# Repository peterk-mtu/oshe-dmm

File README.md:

# oshe-dmm
open source hardware enterprise digital multimeter project

# Photo of our proposed design

# Screenshot of the start to our PCB design

# Screenshot of the Final PCB design

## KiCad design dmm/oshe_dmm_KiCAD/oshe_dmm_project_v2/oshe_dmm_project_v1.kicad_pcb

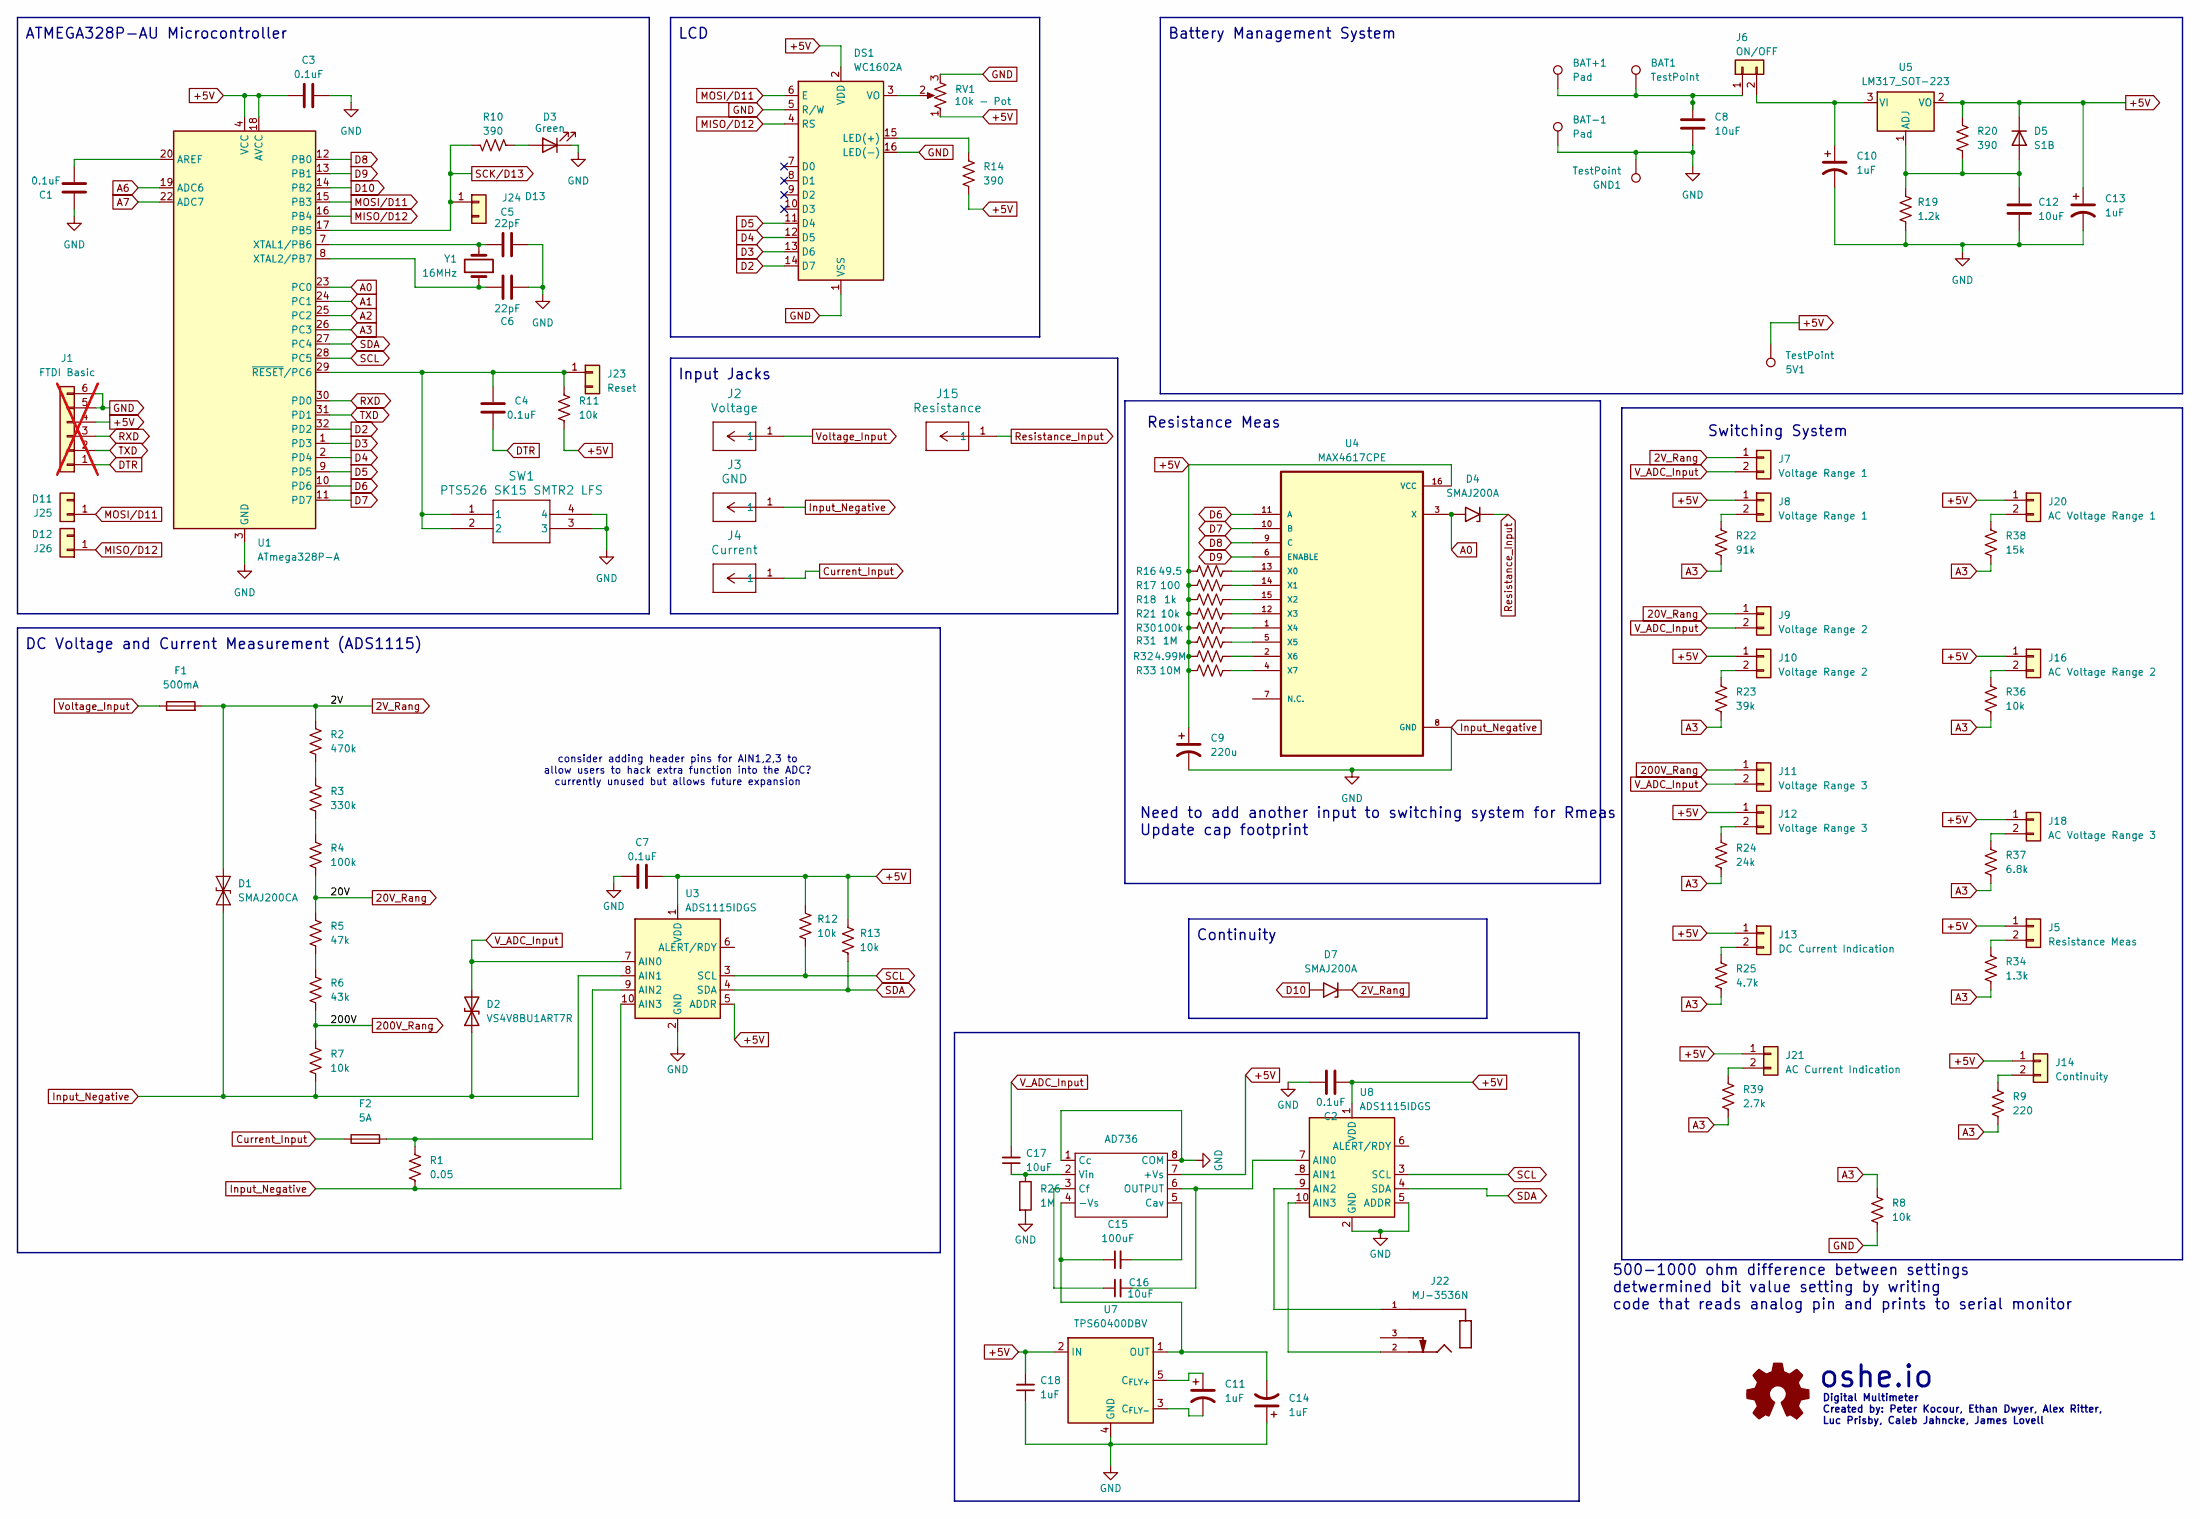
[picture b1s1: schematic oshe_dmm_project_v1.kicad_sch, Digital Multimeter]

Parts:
5V1: TestPoint; TestPoint_Keystone_5019_Minature
BAT1: TestPoint; TestPoint_Keystone_5019_Minature
BAT+1: Pad; TestPoint_THTPad_D4.0mm_Drill2.0mm
BAT-1: Pad; TestPoint_THTPad_D4.0mm_Drill2.0mm
C1, C2, C3, C4, C7: 0.1uF; C_1206_3216Metric_Pad1.33x1.80mm_HandSolder
C5, C6: 22pF; C_1206_3216Metric_Pad1.33x1.80mm_HandSolder
C8, C12, C16, C17: 10uF; C_1206_3216Metric_Pad1.33x1.80mm_HandSolder
C9: 220u; CP_Radial_D6.3mm_P2.50mm
C10, C11, C13, C14, C18: 1uF; CP_Elec_4x4.5
C15: 100uF; CAPC3216X190N
D1: SMAJ200CA; D_SMA
D2: VS4V8BU1ART7R; D_0805_2012Metric_Pad1.15x1.40mm_HandSolder
D3: Green; LED_1206_3216Metric_Pad1.42x1.75mm_HandSolder
D4, D7: SMAJ200A; D_SMA
D5: S1B; D_SMA
DS1: WC1602A
F1: 500mA; FUSE_4628
F2: 5A; FUSE_4628
GND1: TestPoint; TestPoint_Keystone_5019_Minature
J1: FTDI Basic; PinSocket_1x06_P2.54mm_Vertical; not fitted
J2: Voltage; CONN_575-8_KEY
J3: GND; CONN_575-8_KEY
J4: Current; CONN_575-8_KEY
J5: Resistance Meas; PinHeader_1x02_P2.54mm_Vertical
J6: ON/OFF; PinHeader_1x02_P2.54mm_Vertical
J7, J8: Voltage Range 1; PinHeader_1x02_P2.54mm_Vertical
J9, J10: Voltage Range 2; PinHeader_1x02_P2.54mm_Vertical
J11, J12: Voltage Range 3; PinHeader_1x02_P2.54mm_Vertical
J13: DC Current Indication; PinHeader_1x02_P2.54mm_Vertical
J14: Continuity; PinHeader_1x02_P2.54mm_Vertical
J15: Resistance; CONN_575-8_KEY
J16: AC Voltage Range 2; PinHeader_1x02_P2.54mm_Vertical
J18: AC Voltage Range 3; PinHeader_1x02_P2.54mm_Vertical
J20: AC Voltage Range 1; PinHeader_1x02_P2.54mm_Vertical
J21: AC Current Indication; PinHeader_1x02_P2.54mm_Vertical
J22: MJ-3536N; SAMESKY_MJ-3536N; PARTREV 1.05
J23: Reset; PinHeader_1x01_P2.54mm_Vertical
J24: D13; PinHeader_1x01_P2.54mm_Vertical
J25: D11; PinHeader_1x01_P2.54mm_Vertical
J26: D12; PinHeader_1x01_P2.54mm_Vertical
R1: 0.05; R_2512_6332Metric_Pad1.40x3.35mm_HandSolder
R2: 470k; R_1206_3216Metric_Pad1.30x1.75mm_HandSolder
R3: 330k; R_1206_3216Metric_Pad1.30x1.75mm_HandSolder
R4, R30: 100k; R_1206_3216Metric_Pad1.30x1.75mm_HandSolder
R5: 47k; R_1206_3216Metric_Pad1.30x1.75mm_HandSolder
R6: 43k; R_1206_3216Metric_Pad1.30x1.75mm_HandSolder
R7, R8, R11, R12, R13, R21, R36: 10k; R_1206_3216Metric_Pad1.30x1.75mm_HandSolder
R9: 220; R_1206_3216Metric_Pad1.30x1.75mm_HandSolder
R10, R14, R20: 390; R_1206_3216Metric_Pad1.30x1.75mm_HandSolder
R16: 49.5; R_1206_3216Metric_Pad1.30x1.75mm_HandSolder
R17: 100; R_1206_3216Metric_Pad1.30x1.75mm_HandSolder
R18: 1k; R_1206_3216Metric_Pad1.30x1.75mm_HandSolder
R19: 1.2k; R_1206_3216Metric_Pad1.30x1.75mm_HandSolder
R22: 91k; R_1206_3216Metric_Pad1.30x1.75mm_HandSolder
R23: 39k; R_1206_3216Metric_Pad1.30x1.75mm_HandSolder
R24: 24k; R_1206_3216Metric_Pad1.30x1.75mm_HandSolder
R25: 4.7k; R_1206_3216Metric_Pad1.30x1.75mm_HandSolder
R26, R31: 1M; R_1206_3216Metric_Pad1.30x1.75mm_HandSolder
R32: 4.99M; R_1206_3216Metric_Pad1.30x1.75mm_HandSolder
R33: 10M; R_1206_3216Metric_Pad1.30x1.75mm_HandSolder
R34: 1.3k; R_1206_3216Metric_Pad1.30x1.75mm_HandSolder
R37: 6.8k; R_1206_3216Metric_Pad1.30x1.75mm_HandSolder
R38: 15k; R_1206_3216Metric_Pad1.30x1.75mm_HandSolder
R39: 2.7k; R_1206_3216Metric_Pad1.30x1.75mm_HandSolder
RV1: 10k - Pot; Potentiometer_Bourns_3266Y_Vertical
SW1: PTS526 SK15 SMTR2 LFS; SMT_FS
U1: ATmega328P-A; TQFP-32_7x7mm_P0.8mm
U2: AD736; PDIP-8_N
U3, U8: ADS1115IDGS; MODULE_ZC261500
U4: MAX4617CPE
U5: LM317_SOT-223; SOT-223-3_TabPin2
U7: TPS60400DBV; SOT-23-5
Y1: 16MHz; Crystal_HC49-U_Vertical

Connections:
2V_Rang: D1.1 (A1), D7.1 (A1), F1.2, J7.1, R2.1
20V_Rang: J9.1, R4.2, R5.1
200V_Rang: J11.1, R6.2, R7.1
+5V: 5V1.1, C2.1, C3.1, C7.2, C9.1, C13.1, C18.2, D5.1 (K), DS1.2 (VDD), J1.4, J5.1, J8.1, J10.1, J12.1, J13.1, J14.1, J16.1, J18.1, J20.1, J21.1, R11.2, R12.1, R13.1, R14.1, R16.1, R17.1, R18.1, R20.1, R21.1, R30.1, R31.1, R32.1, R33.1, RV1.1, U1.4 (VCC), U1.6 (VCC), U1.18 (AVCC), U2.7 (+Vs), U3.1 (VDD), U3.5 (ADDR), U4.16 (VCC), U5.2 (VO), U7.2 (IN), U8.1 (VDD)
A0: D4.2 (A2), U1.23 (PC0), U4.3 (X)
A1: U1.24 (PC1)
A2: U1.25 (PC2)
A3: R8.2, R9.1, R22.1, R23.1, R24.1, R25.1, R34.1, R36.1, R37.1, R38.1, R39.1, U1.26 (PC3)
A6: U1.19 (ADC6)
A7: U1.22 (ADC7)
Current_Input: F2.1, J4.1
D2: DS1.14 (D7), U1.32 (PD2)
D3: DS1.13 (D6), U1.1 (PD3)
D4: DS1.12 (D5), U1.2 (PD4)
D5: DS1.11 (D4), U1.9 (PD5)
D6: U1.10 (PD6), U4.11 (A)
D7: U1.11 (PD7), U4.10 (B)
D8: U1.12 (PB0), U4.9 (C)
D9: U1.13 (PB1), U4.6 (ENABLE)
D10: D7.2 (A2), U1.14 (PB2)
DTR: C4.2, J1.1
GND: BAT-1.1, C1.1, C2.2, C3.2, C5.2, C6.1, C7.1, C8.2, C9.2, C10.2, C12.2, C13.2, C14.1, C18.1, D1.2 (A2), D2.1 (A1), D3.1 (K), DS1.1 (VSS), DS1.5 (R/W), DS1.16 (LED(-)), GND1.1, J1.5, J1.6, J3.1, R1.2, R7.2, R8.1, R19.2, R26.2, RV1.3, SW1.3, SW1.4, U1.3 (GND), U1.5 (GND), U1.21 (GND), U2.1 (Cc), U2.8 (COM), U3.2 (GND), U3.8 (AIN1), U3.10 (AIN3), U4.8 (GND), U7.4 (GND), U8.2 (GND), U8.5 (ADDR)
MISO/D12: DS1.4 (RS), J26.1, U1.16 (PB4)
MOSI/D11: DS1.6 (E), J25.1, U1.15 (PB3)
unnamed: D3.2 (A), R10.1
unnamed: C12.1, D5.2 (A), R19.1, R20.2, U5.1 (ADJ)
unnamed: DS1.15 (LED(+)), R14.2
unnamed: DS1.3 (VO), RV1.2
unnamed: J5.2, R34.2
unnamed: BAT1.1, BAT+1.1, C8.1, J6.1
unnamed: C10.1, J6.2, U5.3 (VI)
unnamed: J8.2, R22.2
unnamed: J10.2, R23.2
unnamed: J12.2, R24.2
unnamed: J13.2, R25.2
unnamed: J14.2, R9.2
unnamed: J16.2, R36.2
unnamed: J18.2, R37.2
unnamed: J20.2, R38.2
unnamed: J21.2, R39.2
unnamed: C4.1, J23.1, R11.1, SW1.1, SW1.2, U1.29 (~RESET/PC6)
unnamed: R2.2, R3.1
unnamed: R3.2, R4.1
unnamed: R5.2, R6.1
unnamed: C1.2, U1.20 (AREF)
unnamed: C5.1, U1.7 (XTAL1/PB6), Y1.2
unnamed: C6.2, U1.8 (XTAL2/PB7), Y1.1
unnamed: C14.2, C15.1, U2.4 (-Vs), U7.1 (OUT)
unnamed: C15.2, U2.5 (Cav)
unnamed: C16.1, U2.3 (Cf)
unnamed: C16.2, U2.6 (OUTPUT), U8.7 (AIN0)
unnamed: C17.1, R26.1, U2.2 (Vin)
unnamed: F2.2, R1.1, U3.9 (AIN2)
unnamed: R16.2, U4.13 (X0)
unnamed: R17.2, U4.14 (X1)
unnamed: R18.2, U4.15 (X2)
unnamed: R21.2, U4.12 (X3)
unnamed: R30.2, U4.1 (X4)
unnamed: R31.2, U4.5 (X5)
unnamed: R32.2, U4.2 (X6)
unnamed: R33.2, U4.4 (X7)
unnamed: C11.1, U7.5 (C_{FLY+})
unnamed: C11.2, U7.3 (C_{FLY-})
unnamed: J22.1, U8.9 (AIN2)
unnamed: J22.2, U8.10 (AIN3)
RXD: J1.3, U1.30 (PD0)
Resistance_Input: D4.1 (A1), J15.1
SCK/D13: J24.1, R10.2, U1.17 (PB5)
SCL: R12.2, U1.28 (PC5), U3.3 (SCL), U8.3 (SCL)
SDA: R13.2, U1.27 (PC4), U3.4 (SDA), U8.4 (SDA)
TXD: J1.2, U1.31 (PD1)
V_ADC_Input: C17.2, D2.2 (A2), J7.2, J9.2, J11.2, U3.7 (AIN0)
Voltage_Input: F1.1, J2.1

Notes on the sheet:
Digital Multimeter Created by: Peter Kocour, Ethan Dwyer, Alex Ritter, Luc Prisby, Caleb Jahncke, James Lovell
Need to add another input to switching system for Rmeas Update cap footprint
consider adding header pins for AIN1,2,3 to allow users to hack extra function into the ADC? currently unused but allows future expansion
Resistance Meas
oshe.io
Switching System
Battery Management System
DC Voltage and Current Measurement (ADS1115)
LCD
500-1000 ohm difference between settings detwermined bit value setting by writing code that reads analog pin and prints to serial monitor
Input Jacks
Continuity
ATMEGA328P-AU Microcontroller

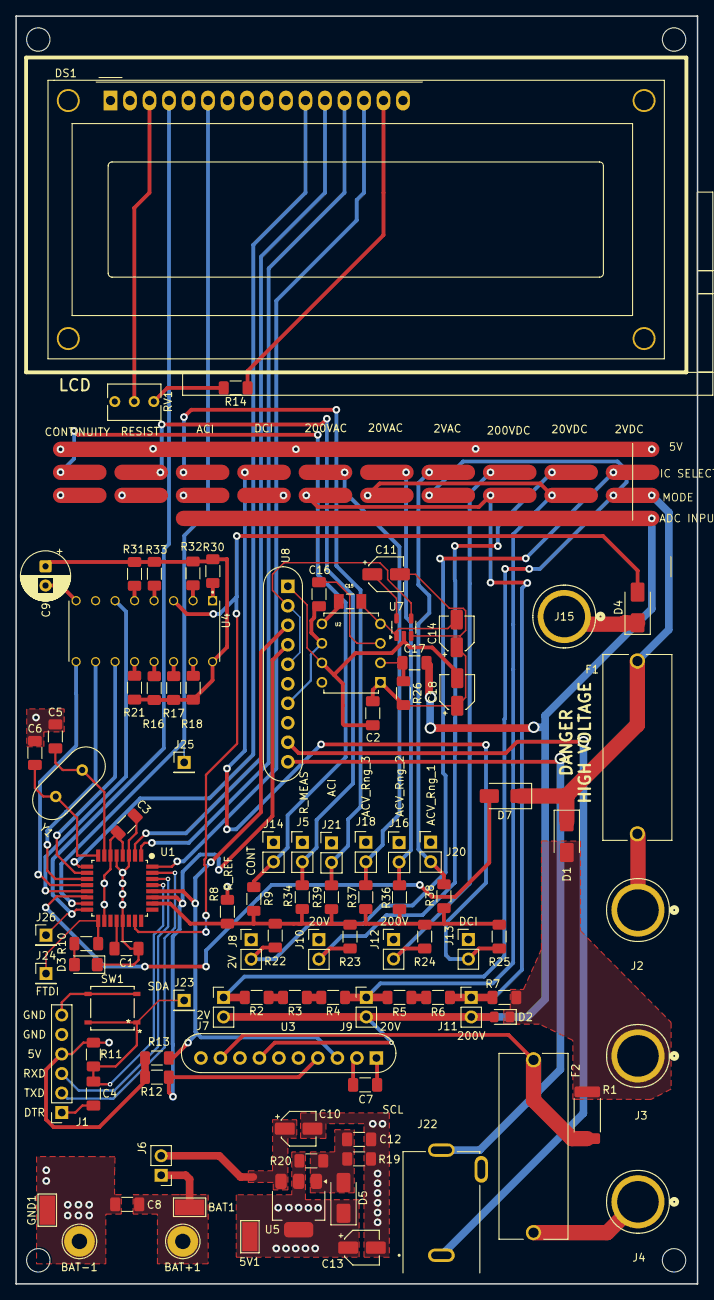
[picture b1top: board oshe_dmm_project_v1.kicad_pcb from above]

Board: 4 copper layers, 88.7 x 165.1 mm, 100 parts (0 on the bottom side), 69 nets.

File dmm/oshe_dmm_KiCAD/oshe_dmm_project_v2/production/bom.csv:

Designator,Footprint,Quantity,Value,LCSC Part #
"5V1, BAT1, GND1",TestPoint_Keystone_5019_Minature,3,TestPoint,
"BAT+1, BAT-1, THERMISTOR1",TestPoint_THTPad_D4.0mm_Drill2.0mm,3,Pad,
"C1, C2, C3, C4, C7",1206,5,0.1uF,
"C10, C11, C13, C14, C18",CP_Elec_4x4.5,5,1uF,
"C12, C16, C17, C8",1206,4,10uF,
C15,CAPC3216X190N,1,100uF,
"C5, C6",1206,2,22pF,
C9,CP_Radial_D6.3mm_P2.50mm,1,220u,
D1,D_SMA,1,SMAJ200CA,
D2,0805,1,VS4V8BU1ART7R,
D3,1206,1,Green,
"D4, D7",D_SMA,2,SMAJ200A,
D5,D_SMA,1,S1B,
DS1,WC1602A,1,WC1602A,
F1,FUSE_4628,1,500mA,
F2,FUSE_4628,1,5A,
J1,PinSocket_1x06_P2.54mm_Vertical,1,FTDI Basic,
"J10, J9",PinHeader_1x02_P2.54mm_Vertical,2,Voltage Range 2,
"J11, J12",PinHeader_1x02_P2.54mm_Vertical,2,Voltage Range 3,
J13,PinHeader_1x02_P2.54mm_Vertical,1,DC Current Indication,
J14,PinHeader_1x02_P2.54mm_Vertical,1,Continuity,
J16,PinHeader_1x02_P2.54mm_Vertical,1,AC Voltage Range 2,
J18,PinHeader_1x02_P2.54mm_Vertical,1,AC Voltage Range 3,
J2,CONN_575-8_KEY,1,Voltage,
J20,PinHeader_1x02_P2.54mm_Vertical,1,AC Voltage Range 1,
J21,PinHeader_1x02_P2.54mm_Vertical,1,AC Current Indication,
J22,SAMESKY_MJ-3536N,1,MJ-3536N,
J3,CONN_575-8_KEY,1,GND,
J4,CONN_575-8_KEY,1,Current,
J5,PinHeader_1x02_P2.54mm_Vertical,1,Resistance Meas,
J6,PinHeader_1x02_P2.54mm_Vertical,1,ON/OFF,
"J7, J8",PinHeader_1x02_P2.54mm_Vertical,2,Voltage Range 1,
R1,2512,1,0.05,
"R10, R14, R20",1206,3,390,
"R11, R12, R13, R15, R21, R7",1206,6,10k,
R16,1206,1,49.5,
R17,1206,1,100,
"R18, R8",1206,2,1k,
"R19, R24",1206,2,1.2k,
R2,1206,1,470k,
R22,1206,1,180,
R23,1206,1,680,
"R25, R34, R39, R9",1206,4,R?,
"R26, R31",1206,2,1M,
R3,1206,1,330k,
"R30, R4",1206,2,100k,
R32,1206,1,4.99M,
R33,1206,1,10M,
R36,1206,1,2.4k,
R37,1206,1,3k,
R38,1206,1,1.8k,
R5,1206,1,47k,
R6,1206,1,43k,
RV1,Potentiometer_Bourns_3266Y_Vertical,1,10k - Pot,
SW1,SMT_FS,1,PTS526 SK15 SMTR2 LFS,
U1,TQFP-32_7x7mm_P0.8mm,1,ATmega328P-A,
U2,PDIP-8_N,1,AD736,
"U3, U8",MODULE_ZC261500,2,ADS1115IDGS,
U4,DIP794W47P254L1943H457Q16,1,MAX4617CPE,
U5,SOT-223-3_TabPin2,1,LM317_SOT-223,
U7,SOT-23-5,1,TPS60400DBV,
Y1,Crystal_HC49-U_Vertical,1,16MHz,

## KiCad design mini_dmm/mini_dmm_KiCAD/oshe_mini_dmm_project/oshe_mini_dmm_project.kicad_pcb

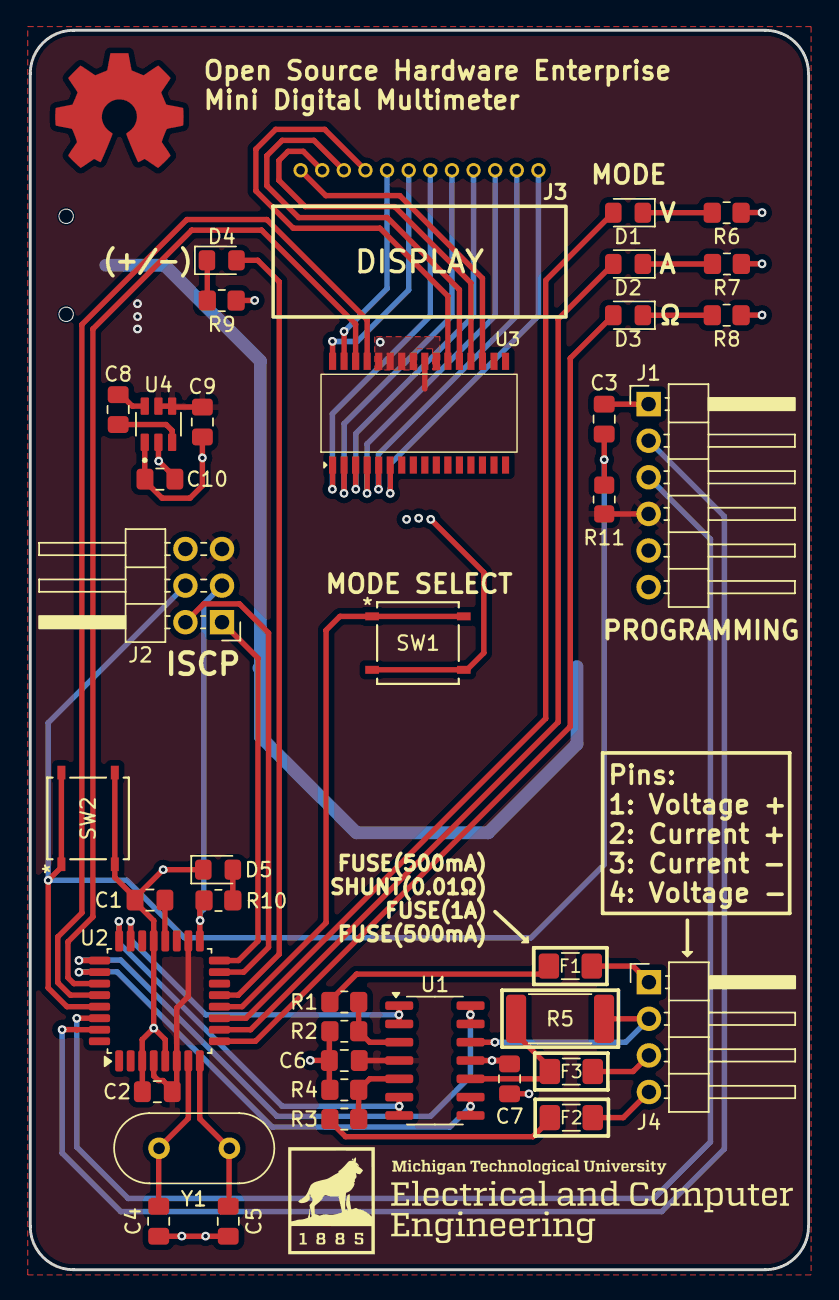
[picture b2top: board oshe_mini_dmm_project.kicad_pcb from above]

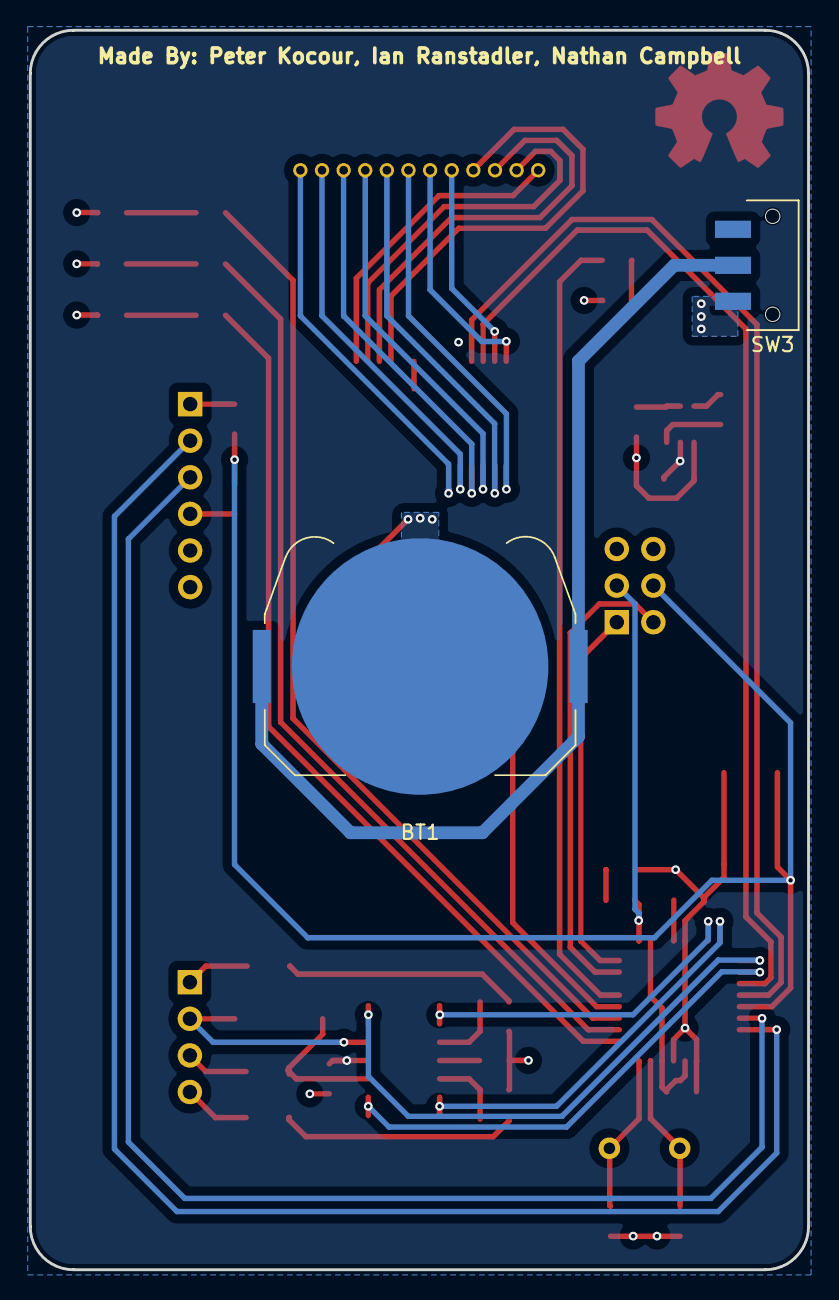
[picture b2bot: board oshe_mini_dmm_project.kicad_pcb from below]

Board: 4 copper layers, 54.0 x 86.0 mm, 42 parts (2 on the bottom side), 53 nets.

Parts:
BT1: Battery; BatteryHolder_Keystone_3034_1x20mm
C1, C2, C3: 0.1uF; C_0805_2012Metric_Pad1.18x1.45mm_HandSolder
C4, C5: 22pF; C_0805_2012Metric_Pad1.18x1.45mm_HandSolder
C6, C7: 1uF; C_0805_2012Metric_Pad1.18x1.45mm_HandSolder
C8, C9, C10: 10uF; C_0805_2012Metric_Pad1.18x1.45mm_HandSolder
D1: VOLTAGE; LED_0805_2012Metric_Pad1.15x1.40mm_HandSolder
D2: CURRENT; LED_0805_2012Metric_Pad1.15x1.40mm_HandSolder
D3: RESISTANCE; LED_0805_2012Metric_Pad1.15x1.40mm_HandSolder
D4: NEGATIVE; LED_0805_2012Metric_Pad1.15x1.40mm_HandSolder
D5: Green; LED_0805_2012Metric_Pad1.15x1.40mm_HandSolder
F1, F2: 500mA; Fuse_1206_3216Metric_Pad1.42x1.75mm_HandSolder
F3: 1A; Fuse_1206_3216Metric_Pad1.42x1.75mm_HandSolder
J1: FTDI Basic; PinHeader_1x06_P2.54mm_Horizontal
J2: ICSP; PinHeader_2x03_P2.54mm_Horizontal
J3: DISPLAY; LCD-S401M16KR-81359
J4: TEST LEAD CONNECTIONS; PinHeader_1x04_P2.54mm_Horizontal
R1, R3: 9.1MEG; R_0805_2012Metric_Pad1.20x1.40mm_HandSolder
R2, R4: 1MEG; R_0805_2012Metric_Pad1.20x1.40mm_HandSolder
R5: 0.05; R_2512_6332Metric_Pad1.40x3.35mm_HandSolder
R6, R7, R8, R9: 1k; R_0805_2012Metric_Pad1.20x1.40mm_HandSolder
R10: 390; R_0805_2012Metric_Pad1.20x1.40mm_HandSolder
R11: 10k; R_0805_2012Metric_Pad1.20x1.40mm_HandSolder
SW1, SW2: PTS526 SK15 SMTR2 LFS; SMT_FS
SW3: SW_DPDT_x2; SW_JS102011SAQN
U1: LM324; SOIC-14_3.9x8.7mm_P1.27mm
U2: ATmega328P-A; TQFP-32_7x7mm_P0.8mm
U3: BU91796FS-ME2; SSOP-A32
U4: LM2664M6; SOT95P280X145-6N
Y1: 16MHz; Crystal_HC49-U_Vertical

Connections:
+3.3V: C2.1, C6.2, C9.2, J1.4, J2.5, R11.2, SW3.1 (A), U1.4 (V+), U2.4 (VCC), U2.6 (VCC), U2.18 (AVCC), U3.24 (VDD), U4.4 (~SD), U4.5 (V+)
-3.3V: C7.1, C10.2, U1.11 (V-), U4.2 (OUT)
/Clock+: C4.1, U2.7 (XTAL1/PB6), Y1.2
/Clock-: C5.2, U2.8 (XTAL2/PB7), Y1.1
A0: U1.1, U1.2 (-), U2.23 (PC0)
A1: U1.6 (-), U1.7, U2.24 (PC1)
A2: U1.13 (-), U1.14, U2.25 (PC2)
A3: U1.8, U1.9 (-), U2.26 (PC3)
A4/SDA: U2.27 (PC4), U3.30 (SDA)
A5/SCL: U2.28 (PC5), U3.29 (SCL)
COM0: J3.1, U3.19 (COM_0)
COM1: J3.2, U3.20 (COM_1)
COM2: J3.3, U3.21 (COM_2)
COM3: J3.4, U3.22 (COM_3)
D5: D3.2 (A), U2.9 (PD5)
D6: D2.2 (A), U2.10 (PD6)
D7: D1.2 (A), U2.11 (PD7)
D8: SW1.1, SW1.2, U2.12 (PB0)
D9: D4.2 (A), U2.13 (PB1)
DTR: C3.2, J1.1
GND: BT1.2 (-), C1.1, C2.2, C4.2, C5.1, C6.1, C7.2, C9.1, C10.1, D5.1 (K), J1.5, J1.6, J2.6, R2.2, R4.2, R6.1, R7.1, R8.1, R9.1, SW1.3, SW1.4, SW2.3, SW2.4, U2.3 (GND), U2.5 (GND), U2.21 (GND), U3.23 (VLCD), U3.25 (VSS), U3.26 (TEST_1), U3.27 (TEST_2), U3.28 (OSCIN), U4.1 (GND)
LEAD_1: F1.1, J4.1
LEAD_2: F2.1, J4.4
LEAD_3: F3.1, J4.3
LEAD_4: J4.2, R5.2, U1.12 (+)
MISO/D12: J2.1, U2.16 (PB4)
MOSI/D11: J2.2, U2.15 (PB3)
unnamed: BT1.1 (+), SW3.2 (B)
unnamed: D1.1 (K), R6.2
unnamed: D2.1 (K), R7.2
unnamed: D3.1 (K), R8.2
unnamed: D4.1 (K), R9.2
unnamed: D5.2 (A), R10.1
unnamed: F1.2, R1.1
unnamed: F2.2, R3.1
unnamed: R1.2, R2.1, U1.3 (+)
unnamed: R3.2, R4.1, U1.5 (+)
unnamed: F3.2, R5.1, U1.10 (+)
unnamed: C1.2, U2.20 (AREF)
unnamed: C8.1, U4.6 (CAP+)
unnamed: C8.2, U4.3 (CAP-)
RESET: C3.1, J2.4, R11.1, SW2.1, SW2.2, U2.29 (~RESET/PC6)
RXD: J1.3, U2.30 (PD0)
SCK/D13: J2.3, R10.2, U2.17 (PB5)
SEG0: J3.5, U3.31 (SEG_0)
SEG1: J3.6, U3.32 (SEG_1)
SEG2: J3.7, U3.1 (SEG_2)
SEG3: J3.8, U3.2 (SEG_3)
SEG4: J3.9, U3.3 (SEG_4)
SEG5: J3.10, U3.4 (SEG_5)
SEG6: J3.11, U3.5 (SEG_6)
SEG7: J3.12, U3.6 (SEG_7)
TXD: J1.2, U2.31 (PD1)

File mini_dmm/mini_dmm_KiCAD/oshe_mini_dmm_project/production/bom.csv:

Designator,Footprint,Quantity,Value,LCSC Part #
BT1,BatteryHolder_Keystone_3034_1x20mm,1,Battery,
"C1, C2, C3",0805,3,0.1uF,
"C10, C8, C9",0805,3,10uF,
"C4, C5",0805,2,22pF,
"C6, C7",0805,2,1uF,
D1,0805,1,VOLTAGE,
D2,0805,1,CURRENT,
D3,0805,1,RESISTANCE,
D4,0805,1,NEGATIVE,
D5,0805,1,Green,
"F1, F2",1206,2,500mA,
F3,1206,1,1A,
J1,PinHeader_1x06_P2.54mm_Horizontal,1,FTDI Basic,
J2,PinHeader_2x03_P2.54mm_Horizontal,1,ICSP,
J3,LCD-S401M16KR-81359,1,DISPLAY,
J4,PinHeader_1x04_P2.54mm_Horizontal,1,TEST LEAD CONNECTIONS,
"R1, R3",0805,2,9.1MEG,
R10,0805,1,390,
R11,0805,1,10k,
"R2, R4",0805,2,1MEG,
R5,2512,1,0.05,
"R6, R7, R8, R9",0805,4,1k,
"SW1, SW2",SMT_FS,2,PTS526 SK15 SMTR2 LFS,
SW3,SW_JS102011SAQN,1,SW_DPDT_x2,
U1,SOIC-14_3.9x8.7mm_P1.27mm,1,LM324,
U2,TQFP-32_7x7mm_P0.8mm,1,ATmega328P-A,
U3,SSOP-A32,1,BU91796FS-ME2,
U4,SOT95P280X145-6N,1,LM2664M6,
Y1,Crystal_HC49-U_Vertical,1,16MHz,

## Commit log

2025-02-07 Created the kicad project files
2025-02-07 Added photos folder and a photo
2025-02-07 Changed photo name
2025-02-07 Fixed README.md
2025-02-07 Started the primary schematic file
2025-02-08 Added BMS to schematic
2025-02-10 Updated main schematic
2025-02-10 Updated things?
2025-02-10 Created an initial PCB
2025-02-10 Made some changes to the PCB
2025-02-10 Made more PCB changes
2025-02-10 Made more changes
2025-02-12 Changed some stuff
2025-02-12 Update Current_Measurement.kicad_sch
    deleted
2025-02-13 Added Current Measurement
2025-02-13 just opened the file
2025-02-13 Took a look at things
2025-02-17 Opened files
2025-02-19 Made changes to PCB and Schematic
2025-02-19 changed resitor symbols
2025-02-19 Made some PCB changes
2025-02-21 Made some changes
2025-02-23 Worked on the PCB
2025-02-24 PCB Design Work
2025-02-25 Made some more PCB changes
2025-02-27 Finalized the BMS system
2025-02-28 Updated input protection schematic.
2025-02-28 Checked some changes
2025-02-28 Made some PCB design changes
2025-02-28 Update Voltage_Measurement.kicad_sch
    James- copied my existing voltage circuit. This is a rough draft that contains the switch and the correct resistor values, but does NOT have the protection stuff we talked about at our last meeting. 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
2025-03-01 Made some PCB and Schematic Changes
2025-03-01 deleted old file
2025-03-01 made some more changes!
2025-03-01 Update oshe_dmm_project_v1.kicad_sch
    Updated voltage schematic.
2025-03-03 Made some changes!
2025-03-03 updated voltage circuit.
    Allows negative voltage measurement
2025-03-03 updated things
2025-03-03 kljlkj
    jlkjlkjlkjl
2025-03-03 kjlkj
    klklj
2025-03-03 Added screenshots!
2025-03-05 More changes plus custom footprints and symbols!
2025-03-08 Friday Library Meeting
2025-03-09 Replaced PCB file with update
2025-03-09 Updated Switch
2025-03-09 Made some updates
2025-03-10 Trying to fit everything on the board
2025-03-10 Zip archive
2025-03-11 Swapped Miso/Mosi Pins
2025-03-11 PCB is almost done!
2025-03-11 More PCB changes!
2025-03-12 Final V1 PCB?!?!?!?
2025-03-12 Updated V1 Board Revision
2025-03-13 updated more stuff
2025-03-14 Final Board complete + BOM
    Final board design is complete and ready to order. Bill of Materials has also been completed.
2025-03-21 deleted unneed stuff
2025-03-21 Code
    Arduino Codes Added
2025-03-21 More code changes
2025-03-24 Update DMM_MainCode.ino
    set pinMode Inputs
2025-03-26 Code Updates
2025-03-26 Lil Update
2025-03-30 Created test circuit schematic and uploaded code to folder
2025-03-30 Added photos
2025-03-31 Generated gbr files
2025-09-04 Moved some folders around
2025-09-04 Created the KiCAD project
2025-09-04 Created new kicad project for dmm
2025-09-04 Revert "Delete DMM directory"
    This reverts commit 6c336f6cfc18ae221bbbf7f589b9bed94631240a.
2025-09-04 new files
2025-09-04 Fixed the location of files
2025-09-04 Moved some stuff around
2025-09-18 added to mini dmm schematic
2025-09-18 edited files
2025-09-25 Added to schematic
2025-10-05 Made some more updates!
2025-10-06 created horizontal switching rail in V2 folder. copied V1 files
2025-10-07 Updated schematic
2025-10-08 Made some more changes
2025-10-08 Exported a BoM
2025-10-16 Made PCB updates
2025-10-17 PCB Updated
2025-10-19 schematic of res meas
2025-10-19 Finished PCB
2025-10-21 Added production files
2025-10-22 Add res to pcb
2025-10-22 edits
2025-10-24 Resistance meas on PCB, need to add lead connections
2025-10-24 finished Resistance
2025-10-25 Moved DC current measurement
    Moved DC current measurement to use the same ADC as DC voltage measurement.
2025-10-26 DC Voltage and Current Update
    The PCB was updated so that only one ADC is used for DC voltage and current measurement. The footprint for the ADC was also updated.
2025-10-26 Exported final board
2025-10-26 Cleaned up holes from deleted vias
2025-10-27 commit?
2025-10-27 Updated PCB
2025-10-28 AC current and voltage measurement
    Updated Schematic and PCB to include AC voltage and current measurement. Also fixed an issue with DC voltage and current ADC had the wrong pin numbers assigned.
2025-10-28 changes PCB
2025-10-28 Finalished PCB
2025-10-28 ughhhhh i need sleep
2025-10-28 Fixed footprint errors
2025-10-28 Fixed silkscreen errors
2025-10-28 Generated Gerber file
2025-10-28 double check
2025-10-28 Zipped files
2025-10-29 Removed buried vias
2025-10-29 Exported new Gerber files.
2025-10-29 Fabricated board with JLC plugin
2025-10-30 updated led resistor
2025-10-30 added firmware for mini_dmm
2025-10-31 Removed a via
    Removed a via that was incorrectly attached to multiple layers.
2025-11-03 Revert "Merge branch 'main' of https://github.com/peterk-mtu/oshe-dmm"
    This reverts commit ce5d962f54be2277657b6d8c67a3a7c391f0a935, reversing
    changes made to f95ec51989ec9ec0648d62f0b87f0342297760cd.
2025-11-06 Combined OSHE DMM code
    This is the skeleton of the OSHE DMM code. Still need to implement the current and voltage reading code fully
2025-11-06 Update files
    Updated 11 am. Just changed the print statements to all be 16 chars
2025-11-07 Completed DMM Code
    finished adding in Voltage and current measurement code
2025-11-10 added STL files
2025-11-11 Last minute changes
    Added header pins to make boot loading easier, removed battery management circuit for the rechargeable version, fixed i2c address pin that was connected to GND instead of 5V.
2025-12-04 Added New Input Probe
    Added a new input probe for resistance measurement. Also fixed the direction of some polarized capacitors.
2025-12-05 footpront names
2025-12-05 Updated files to latest
2025-12-05 footprint
2025-12-05 Added Final Report
